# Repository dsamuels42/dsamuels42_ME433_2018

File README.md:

ME 433
 David Samuels
 
 Contains homeworks and projects for ME433 Spring 2018

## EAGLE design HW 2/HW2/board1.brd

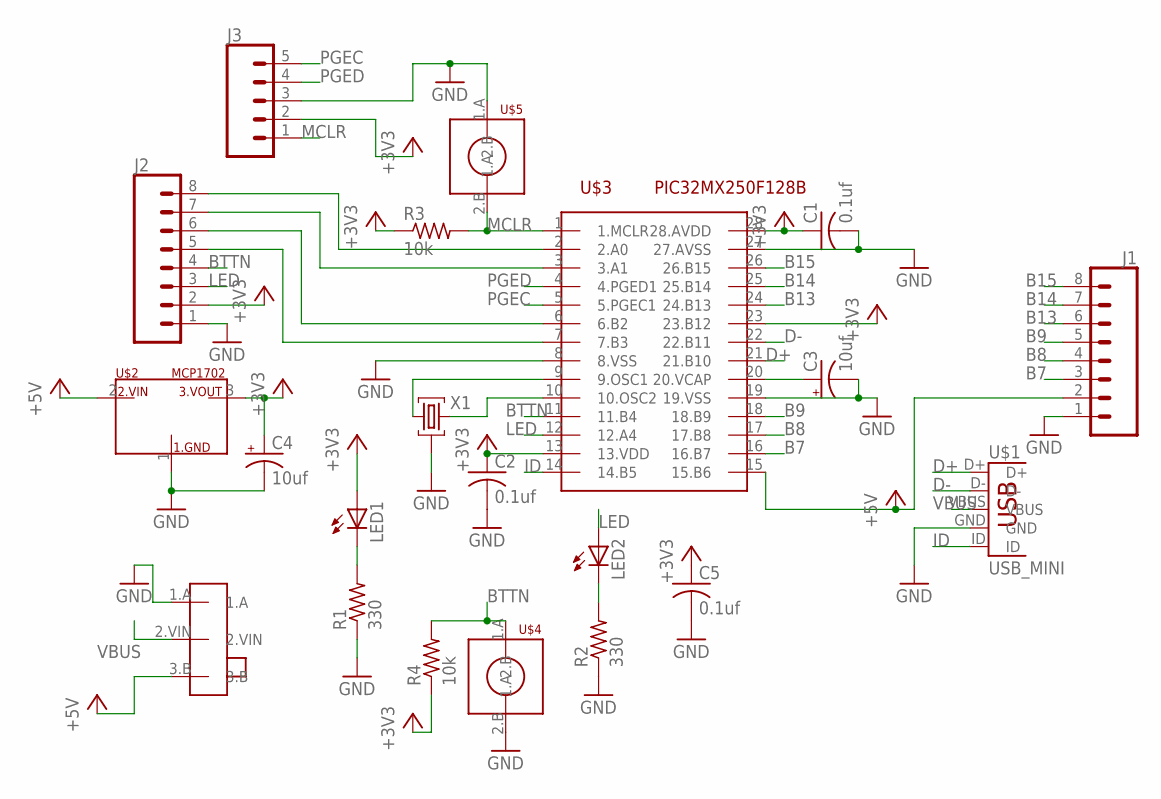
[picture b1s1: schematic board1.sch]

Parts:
C1, C2, C5: 0.1uf; C025-025X050
C3, C4: 10uf; E2,5-6E
J1, J2: CONN_08"; 1X08
J3: CONN_05; 1X05
LED1, LED2: LED5MM
R1, R2: 330; 0204/5
R3, R4: 10k; 0204/5
U$1: USB_MINI; USB-MB-H
U$2: MCP1702; TO92
U$3: PIC32MX250F128B; DIL28-3
U$4, U$5: PUSH_BUTTON
U$6: SLIDE_SWITCH
X1: HC49-HC49-3L; HC49-3L

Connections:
+3V3: C1.1, C2.1, C4.+, C5.1, J2.2, J3.2, LED1.A, R3.1, R4.1, U$2.3 (3.VOUT), U$3.13 (13.VDD), U$3.23 (23.B12), U$3.28 (28.AVDD)
+5V: J1.2, U$2.2 (2.VIN), U$3.15 (15.B6), U$6.3.B
B7: J1.3, U$3.16 (16.B7)
B8: J1.4, U$3.17 (17.B8)
B9: J1.5, U$3.18 (18.B9)
B13: J1.6, U$3.24 (24.B13)
B14: J1.7, U$3.25 (25.B14)
B15: J1.8, U$3.26 (26.B15)
BTTN: J2.4, R4.2, U$3.11 (11.B4), U$4.1.A
D+: U$1.D+, U$3.21 (21.B10)
D-: U$1.D-, U$3.22 (22.B11)
GND: C1.2, C2.2, C3.-, C4.-, C5.2, J1.1, J2.1, J3.3, R1.1, R2.1, U$1.GND, U$2.1 (1.GND), U$3.8 (8.VSS), U$3.19 (19.VSS), U$3.27 (27.AVSS), U$4.2.B, U$5.1.A, U$6.1.A, X1.2
ID: U$1.ID, U$3.14 (14.B5)
LED: J2.3, LED2.A, U$3.12 (12.A4)
MCLR: J3.1, R3.2, U$3.1 (1.MCLR), U$5.2.B
unnamed: LED1.K (C), R1.2
unnamed: LED2.K (C), R2.2
unnamed: U$3.10 (10.OSC2), X1.3
unnamed: U$3.9 (9.OSC1), X1.1
unnamed: C3.+, U$3.20 (20.VCAP)
unnamed: J2.8, U$3.2 (2.A0)
unnamed: J2.7, U$3.3 (3.A1)
unnamed: J2.6, U$3.6 (6.B2)
unnamed: J2.5, U$3.7 (7.B3)
PGEC: J3.5, U$3.5 (5.PGEC1)
PGED: J3.4, U$3.4 (4.PGED1)
VBUS: U$1.VBUS, U$6.2.VIN

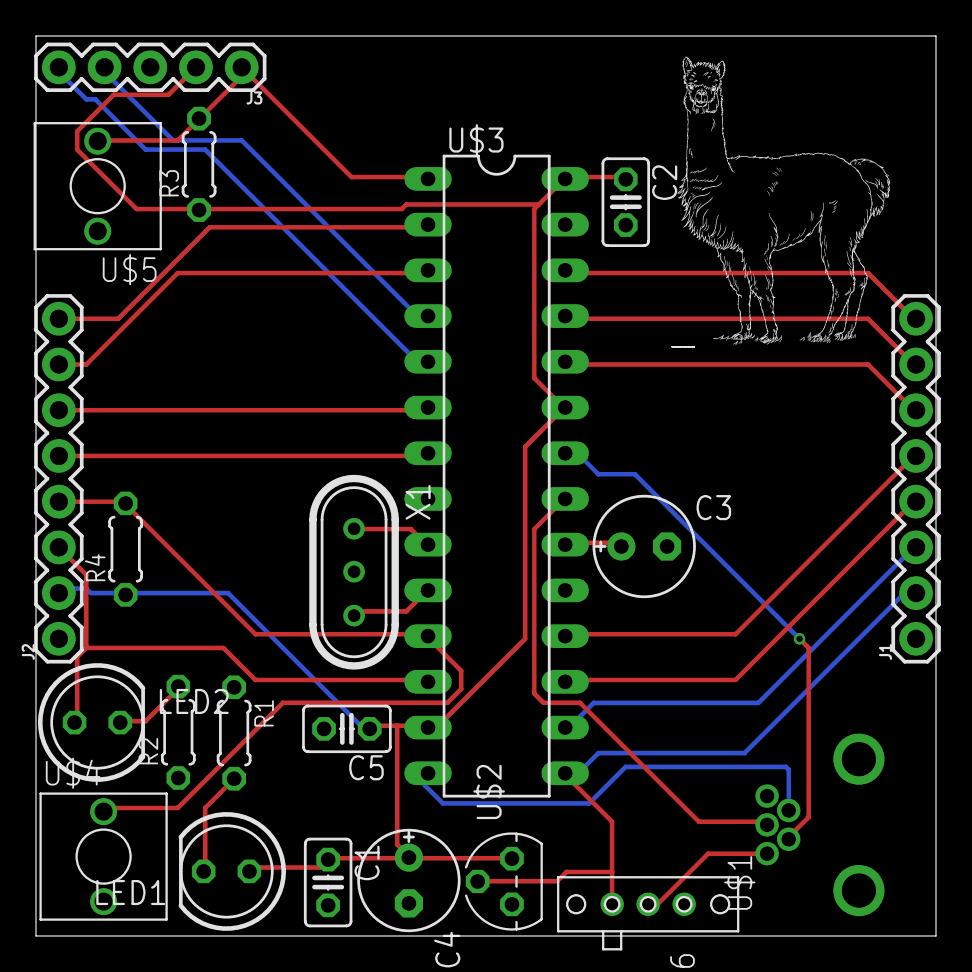
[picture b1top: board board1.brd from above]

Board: 2 copper layers, 50.0 x 50.0 mm, 21 parts (0 on the bottom side), 27 nets.

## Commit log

2018-04-05 added remote pic32 documentation
2018-04-05 added code template
2018-04-05 fix readme because git took \n literally
2018-04-09 Add HW1 Project
2018-04-10 Completed code for HW 1
2018-04-10 added images
2018-04-10 Added circuit diagram
2018-04-16 HW2
    Completed eagle schematic
2018-04-16 HW3
    Completed PCB layout and routing
2018-04-16 added zip
2018-04-24 added a lot from h4, h5, and h6
2018-05-22 Stuff from H5 H6 and H12
2018-05-22 HW 13
2018-06-09 Finished HW 4 - 7
2018-06-09 HW 8
2018-06-10 HW 9
2018-06-12 HW 10
2018-06-12 HW 11
2018-06-12 fix to HW 13
2018-06-12 HW 14, accidentally across two folders
2018-06-13 HW 16
2018-06-13 HW 17
2018-06-14 HW 18
2018-06-14 hw 18 photos
